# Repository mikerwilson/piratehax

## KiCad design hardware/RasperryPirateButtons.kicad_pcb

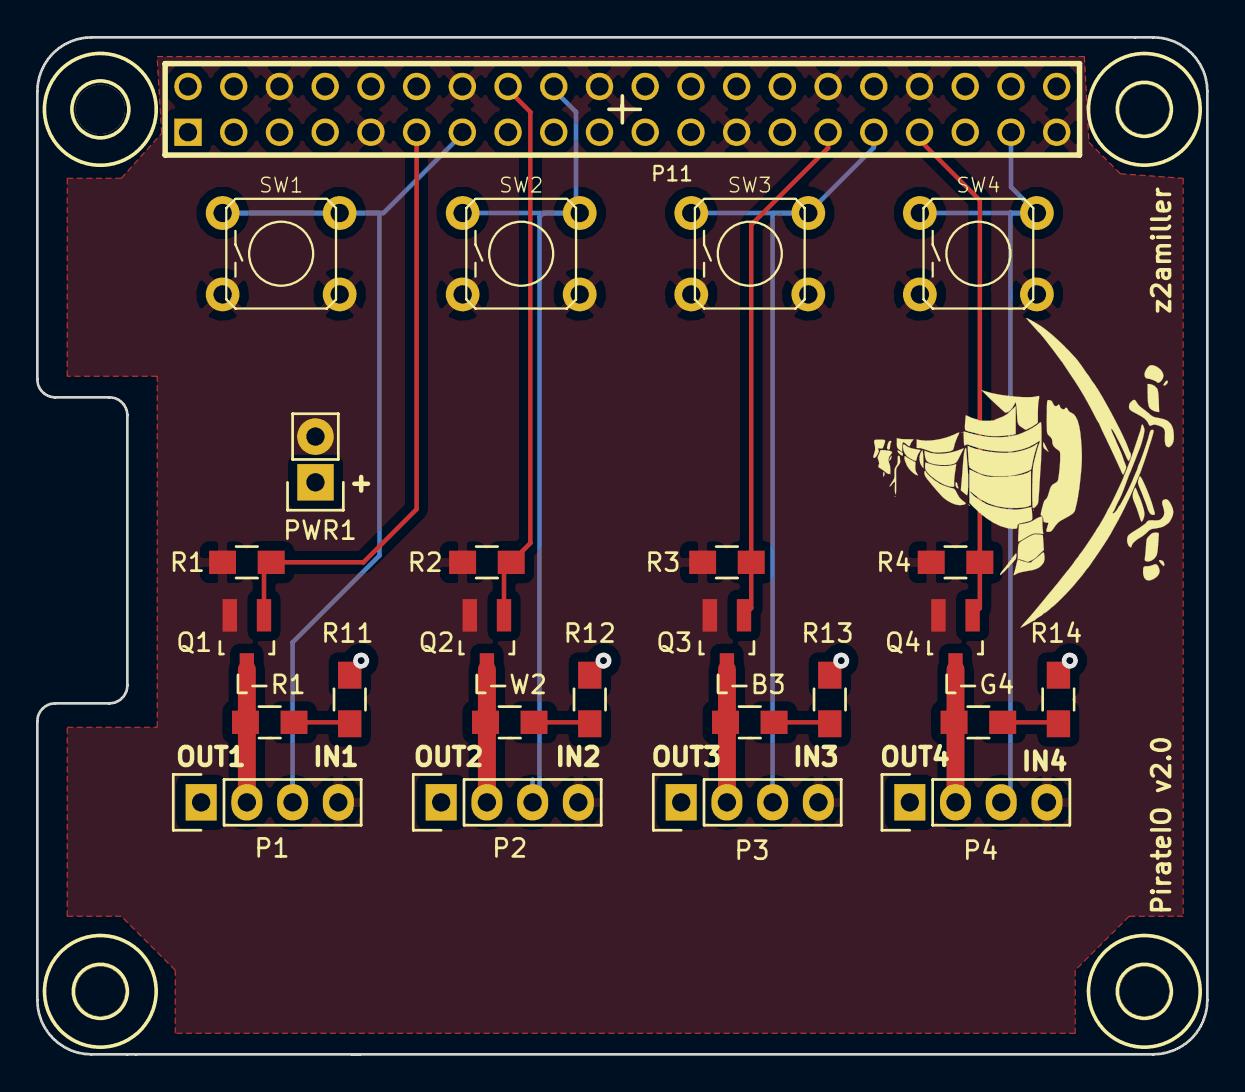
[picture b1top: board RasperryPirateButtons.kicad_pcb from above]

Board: 2 copper layers, 65.0 x 56.5 mm, 30 parts (0 on the bottom side), 18 nets.

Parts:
H1, H2, H3, H4: DRILL; dsk-drill-rpi-hat
L-B3: LED-B; R_0805_HandSoldering
L-G4: LED-G; R_0805_HandSoldering
L-R1: LED-R; R_0805_HandSoldering
L-W2: LED-W; R_0805_HandSoldering
P1, P2, P3, P4: CONN_01X04; Pin_Header_Straight_1x04
P11: CONN_20X2; PIN_ARRAY_20X2
PWR1: CONN_01X02; Pin_Header_Straight_1x02
Q1, Q2, Q3, Q4: AO3400; SOT-23_Handsoldering
R1, R2, R3, R4: 100K; R_0805_HandSoldering
R11, R12, R13, R14: 560; R_0805_HandSoldering
SW1, SW2, SW3, SW4: BG SW; AB2_PB_MOM_6MM_PTH_BLK

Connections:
+12V: P1.1, P2.1, P3.1, P4.1, PWR1.1, R11.2, R12.2, R13.2, R14.2
GND: P1.4, P2.4, P3.4, P4.4, P11.6, P11.9, P11.14, P11.20, P11.25, P11.30, P11.34, P11.39, PWR1.2, Q1.2, Q2.2, Q3.2, Q4.2, R1.2, R2.2, R3.2, R4.2, SW1.2, SW2.2, SW3.2, SW4.2
GPIO05: P11.29, Q3.1, R3.1
GPIO06: P3.3, P11.31, SW3.1
GPIO13: P11.33, Q4.1, R4.1
GPIO17: P11.11, Q1.1, R1.1
GPIO23: P11.16, Q2.1, R2.1
GPIO24: P2.3, P11.18, SW2.1
GPIO26: P4.3, P11.37, SW4.1
GPIO27: P1.3, P11.13, SW1.1
unnamed: L-B3.1, P3.2, Q3.3
unnamed: L-B3.2, R13.1
unnamed: L-G4.1, P4.2, Q4.3
unnamed: L-G4.2, R14.1
unnamed: L-R1.1, P1.2, Q1.3
unnamed: L-R1.2, R11.1
unnamed: L-W2.1, P2.2, Q2.3
unnamed: L-W2.2, R12.1

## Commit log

2015-10-02 Initial commit of button controller board
2015-10-02 Added plots of the schematic and board layout.
2015-10-06 Cleanup and fix comments.
2015-10-11 Version 2 of pirate buttons
2015-10-11 Better +12v connection, plotted gerber files.
2015-10-14 Added single button pwm test script
2015-10-29 Add tester for PWMing on all four buttons.
